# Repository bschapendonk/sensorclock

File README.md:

# sensorclock

I'm a software engineer by trade and I was looking for a nice project to use [Windows 10 IoT Core](https://dev.windows.com/en-us/iot) running on a Raspberry Pi 2 Model B.
So I decided on an clock inspired by Steve Gardner's [6 Digit LED Clock](http://sdgelectronics.co.uk/ledclock-projects/) project.
Initially I only planned on the clock, but I ended up addeding a bunch of sensors that might be used for some "IoT" in the feature.

Everything is controlled thru I2C, except the RGB leds which use SPI, some GPIO's for the rotary encoder, interrupts from the sensors and control lines to turn off the +3V3 (to reset all I2C devices). Basically any MCU that has I2C, SPI and some GPIO's can be used.

*The new Raspberry Pi 3 is pin compatible and runs even better*

* [Schematic](/hardware/pdf/sensorclock.pdf)
* [Board Top](/hardware/pdf/sensorclock_top.pdf)
* [Board Bottom](/hardware/pdf/sensorclock_bottom.pdf)
* [Gerbers](/hardware/gerber)

## things learned / improvements / mistakes
* U2 has an invalid I2C address
 * [Workaround] Use ALLCALL to enable SUBADDR1 on all PCA9622's, then disable SUBADDR1 on the good addressed PCA9622's and use SUBADDR1 to address the wrong addressed U2
* The MCP3425 and DS3231 have the same I2C address #fail
 * [Workaround] For now I cut the SDA/SCL traces to the DS3231
* The interconnect between te sensorclock and the Raspberrry Pi 2
 * This is a custom cable which saved time in design process of the board (less complex routing), but in hindsight this was a mistake since the assembly of the cable is quite difficult and error prone.
 
## features
* Windows 10 IoT Core controlled
* Six 7-segment 70mm (2.3") high displays
* Eight APA102C serial controlled RGB led's for ambient lighting or mood indication
* Temperature, humidity, barometric pressure, ambient light and air quality sensors
* Mechanical rotary encoder with switch for user input

## components
* Raspberry Pi 2 Model B
* ~~DS3231 [http://datasheets.maximintegrated.com/en/ds/DS3231.pdf]~~ (address conflict)
* PEC16 [http://www.bourns.com/data/global/pdfs/pec16.pdf]
* APA102C [http://www.adafruit.com/datasheets/APA102.pdf]

### clock
* PCA9622 [http://www.nxp.com/documents/data_sheet/PCA9622.pdf]
* SA23-11SRWA [http://www.kingbrightusa.com/images/catalog/spec/SA23-11SRWA.pdf]

### sensors
* SparkFun Atmospheric Sensor Breakout - BME280 [https://www.sparkfun.com/products/13676]
* SparkFun Luminosity Sensor Breakout - TSL2561 [https://www.sparkfun.com/products/12055]
* MQ-135 air quality sensor, ADC and loadswitch
 * MCP3425 [http://ww1.microchip.com/downloads/en/DeviceDoc/22072b.pdf]
 * AP2280 [http://www.diodes.com/_files/datasheets/AP2280.pdf]

**!!This is a work in progress, use at your own risk!!**

## renders

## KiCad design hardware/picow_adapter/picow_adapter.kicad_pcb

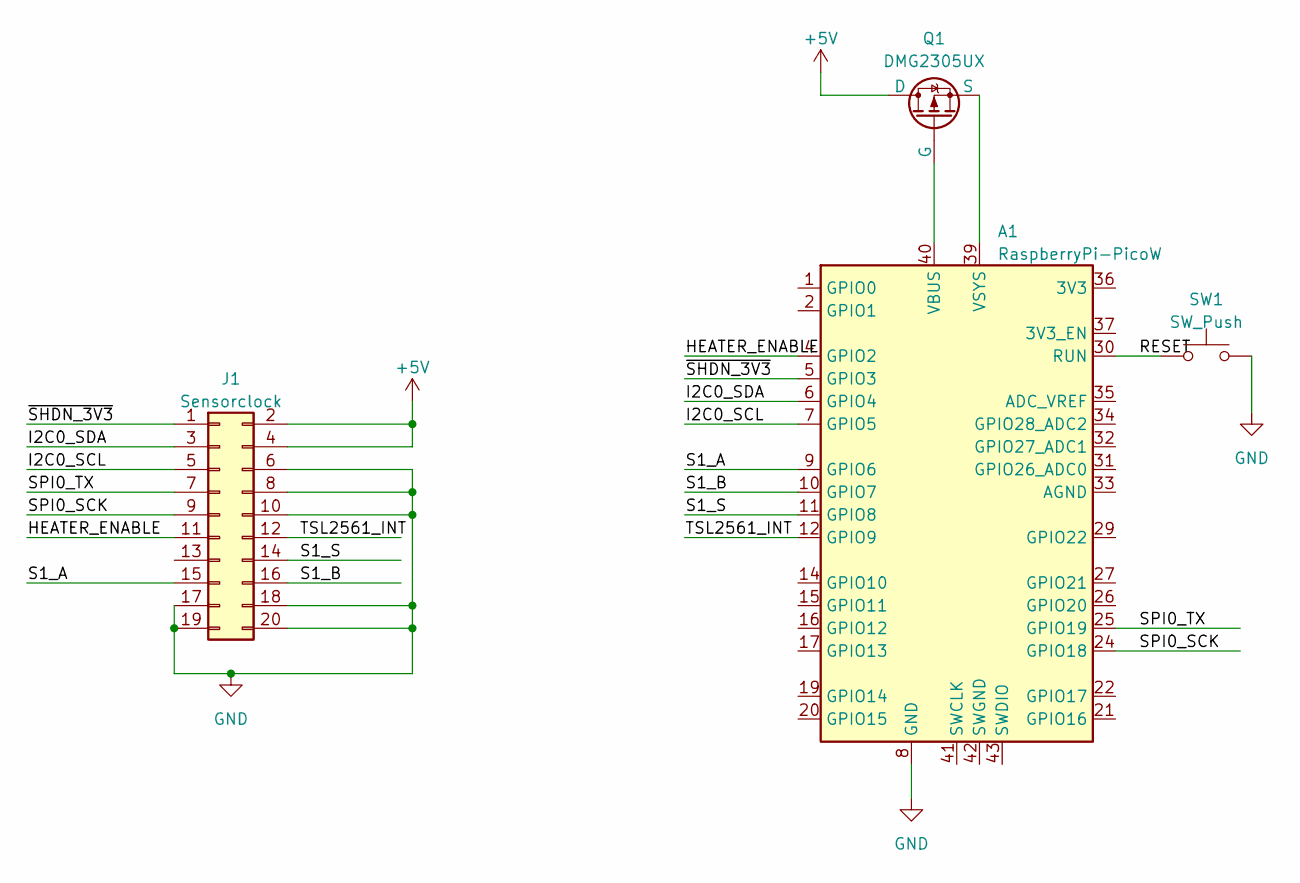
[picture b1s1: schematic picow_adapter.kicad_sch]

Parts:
A1: RaspberryPi-PicoW; Raspberry_Pi_Pico_SMT_THT
J1: Sensorclock; PinSocket_2x10_P2.54mm_Vertical
Q1: DMG2305UX; SOT-23
SW1: SW_Push; SW_SPST_B3U-1000P

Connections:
+5V: J1.2, J1.4, Q1.3 (D)
/HEATER_ENABLE: A1.4 (GPIO2), J1.11
/I2C0_SCL: A1.7 (GPIO5), J1.5
/I2C0_SDA: A1.6 (GPIO4), J1.3
/RESET: A1.30 (RUN), SW1.1
/S1_A: A1.9 (GPIO6), J1.15
/S1_B: A1.10 (GPIO7), J1.16
/S1_S: A1.11 (GPIO8), J1.14
/SPI0_SCK: A1.24 (GPIO18), J1.9
/SPI0_TX: A1.25 (GPIO19), J1.7
/TSL2561_INT: A1.12 (GPIO9), J1.12
/~SHDN_3V3: A1.5 (GPIO3), J1.1
GND: A1.3 (GND), A1.8 (GND), A1.13 (GND), A1.18 (GND), A1.23 (GND), A1.28 (GND), A1.38 (GND), J1.6, J1.8, J1.10, J1.17, J1.18, J1.19, J1.20, SW1.2
unnamed: A1.40 (VBUS), Q1.1 (G)
unnamed: A1.39 (VSYS), Q1.2 (S)

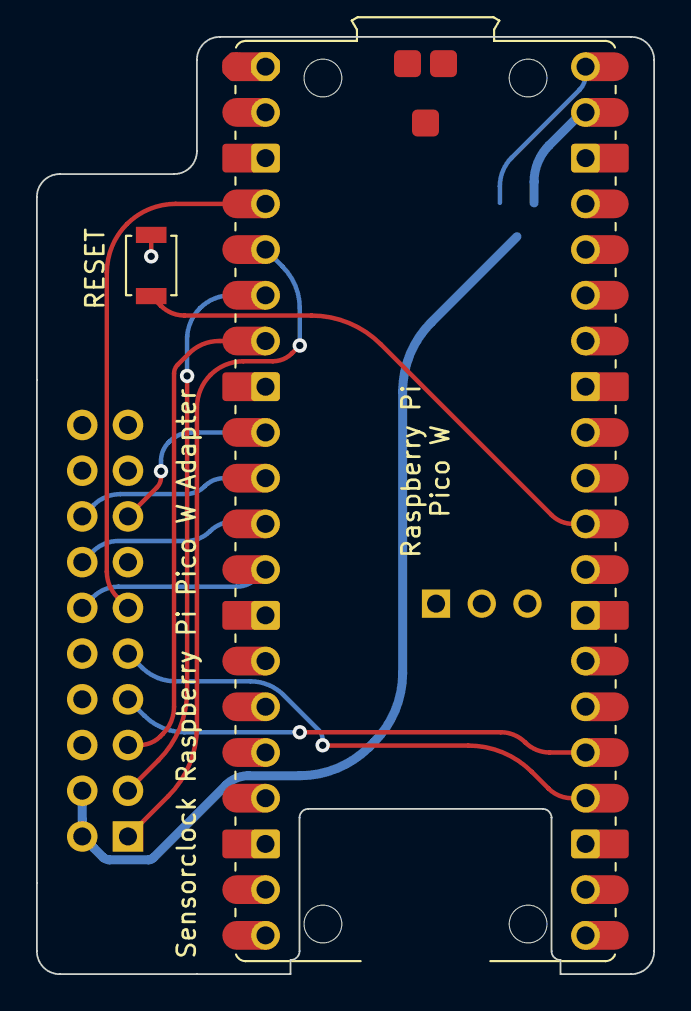
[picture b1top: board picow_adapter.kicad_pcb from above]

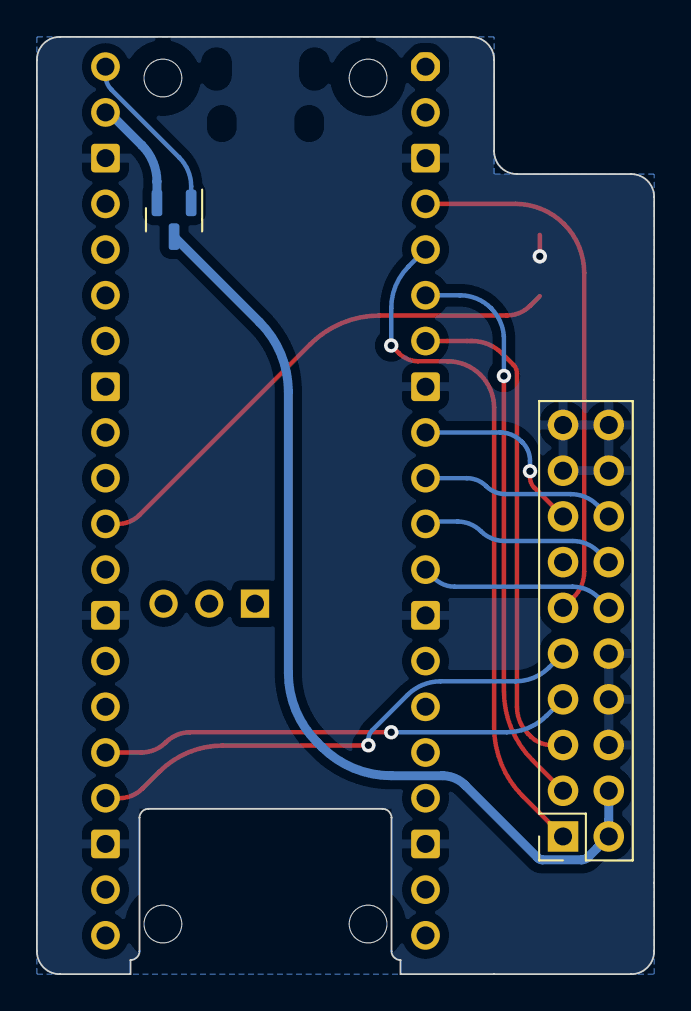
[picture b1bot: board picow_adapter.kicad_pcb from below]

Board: 2 copper layers, 34.3 x 52.1 mm, 4 parts (2 on the bottom side), 15 nets.

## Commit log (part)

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2015-11-09 import
2015-11-15 Fixed an addressing issue with the PCA9622
2015-11-22 inital import
2015-11-22 test programm
2016-02-26 inital
2016-04-12 Microsoft.NETCore.UniversalWindowsPlatform 5.1.0
2016-06-27 Microsoft.NETCore.UniversalWindowsPlatform 5.2.0
2016-07-19 Microsoft.NETCore.UniversalWindowsPlatform 5.2.2
2016-08-09 Target Windows 10 AU
2017-02-21 Microsoft.NETCore.UniversalWindowsPlatform 5.3.0
2017-03-14 Microsoft.NETCore.UniversalWindowsPlatform 5.3.1
2017-04-06 Target 10.0.15063.0
2017-04-11 Microsoft.NETCore.UniversalWindowsPlatform 5.3.2
2017-04-25 Microsoft.NETCore.UniversalWindowsPlatform 5.3.3
2017-04-25 conversion to PackageReference codemaid cleanupall
2017-08-08 Microsoft.NETCore.UniversalWindowsPlatform 5.3.4
2017-08-15 Microsoft.NETCore.UniversalWindowsPlatform 5.4.0
2017-09-01 small improvement
2017-09-01 crude rainbow effect
2017-09-01 timing
2017-10-15 Microsoft.NETCore.UniversalWindowsPlatform 6.0.1
2017-10-19 TargetPlatform 10.0.16299.0
2017-11-22 Microsoft.NETCore.UniversalWindowsPlatform 6.0.2
2017-12-05 Microsoft.NETCore.UniversalWindowsPlatform 6.0.4
2017-12-13 Microsoft.NETCore.UniversalWindowsPlatform 6.0.5
2018-01-10 Microsoft.NETCore.UniversalWindowsPlatform 6.0.6
2018-02-13 Microsoft.NETCore.UniversalWindowsPlatform 6.0.7
2018-05-08 target 10.0.17134.0
2018-05-17 Microsoft.NETCore.UniversalWindowsPlatform 6.1.4
2018-07-03 Microsoft.NETCore.UniversalWindowsPlatform 6.1.5
2018-08-03 Microsoft.NETCore.UniversalWindowsPlatform 6.1.7
2018-10-10 TargetPlatformVersion 10.0.17763.0 Microsoft.NETCore.UniversalWindowsPlatform 6.1.9
2018-12-11 Microsoft.NETCore.UniversalWindowsPlatform 6.2.2
2019-06-12 Microsoft.NETCore.UniversalWindowsPlatform 6.2.8
2021-10-12 .net 6.0 rc2
2021-11-08 .net 6.0 :)
2022-09-22 .NET 7 rc1
2022-09-22 update pipeline
2022-11-16 Raspberry Pi 4B get! Hello World ARM64!
2023-03-23 net8.0 let's GO
2023-03-23 test
2023-03-23 revert
2025-03-19 Update Microsoft.Extensions.Hosting.Systemd package version
    Updated the version of the `Microsoft.Extensions.Hosting.Systemd` package in the `Directory.Packages.props` file from `10.0.0-preview.1.25080.5` to `10.0.0-preview.2.25163.2`.
2025-04-13 Update Microsoft.Extensions.Hosting.Systemd package version
    Updated the version of the `Microsoft.Extensions.Hosting.Systemd` package from `10.0.0-preview.2.25163.2` to `10.0.0-preview.3.25171.5` in the `Directory.Packages.props` file.
2025-05-13 Update Microsoft.Extensions.Hosting.Systemd package version
    Updated the version of the `Microsoft.Extensions.Hosting.Systemd` package in the `Directory.Packages.props` file from `10.0.0-preview.3.25171.5` to `10.0.0-preview.4.25258.110`.
2025-05-14 Revert Microsoft.Extensions.Hosting.Systemd package version to 9.0.5 and update target framework to net9.0
2025-05-14 Restore .NET version to 9 in GitHub Actions workflow
2025-05-15 Fix artifact path to target .NET 9.0 in GitHub Actions workflow
2025-06-13 Update package versions in Directory.Packages.props
    Updated `Iot.Device.Bindings` to version `4.0.1` and
    `Microsoft.Extensions.Hosting.Systemd` to version `9.0.6`.
2025-07-31 Update Microsoft.Extensions.Hosting.Systemd to 9.0.7
    Updated the version of the package `Microsoft.Extensions.Hosting.Systemd` from `9.0.6` to `9.0.7` in the `Directory.Packages.props` file.
2025-08-28 Update actions/checkout to version 5 in GitHub Actions workflow
2025-09-02 Update Microsoft.Extensions.Hosting.Systemd to 9.0.8
    Updated the version of the package `Microsoft.Extensions.Hosting.Systemd` from `9.0.7` to `9.0.8` in the `Directory.Packages.props` file.
2025-09-12 Update Microsoft.Extensions.Hosting.Systemd to 9.0.9
    Updated the version of the package `Microsoft.Extensions.Hosting.Systemd` from `9.0.8` to `9.0.9` in the `Directory.Packages.props` file.
2025-10-20 Update Microsoft.Extensions.Hosting.Systemd to 9.0.10
    Updated the `Directory.Packages.props` file to increment the
    version of the `Microsoft.Extensions.Hosting.Systemd` package
    from `9.0.9` to `9.0.10`. This ensures the project benefits
    from any bug fixes, performance improvements, or new features
    introduced in the updated version. No other package versions
    were modified.
2025-10-20 Update actions/setup-dotnet to version 5 and change dotnet version to 10
2025-11-12 Remove commented dotnet-quality option in workflow configuration
2025-12-09 Update Microsoft.Extensions.Hosting.Systemd to 10.0.1
    Updated the `Microsoft.Extensions.Hosting.Systemd` package version in the `Directory.Packages.props` file from `10.0.0` to `10.0.1`. This minor version update likely includes bug fixes or small impro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
2025-12-22 Upgrade GitHub Actions to latest versions
2026-03-18 #
    Update NuGet package versions for Iot and Systemd
    Upgraded Iot.Device.Bindings from 4.0.1 to 4.1.0 and Microsoft.Extensions.Hosting.Systemd from 10.0.1 to 10.0.5 to include the latest features and fixes.
2026-04-01 Update Iot.Device.Bindings to version 4.2.0
    Upgraded the Iot.Device.Bindings NuGet package from version 4.1.0 to 4.2.0 in Directory.Packages.props to incorporate the latest features and fixes. No other dependencies were changed.
2026-04-15 Update Systemd package to version 10.0.6
    Upgraded Microsoft.Extensions.Hosting.Systemd from 10.0.5 to 10.0.6 in Directory.Packages.props to ensure the latest fixes and improvements are included. No other dependencies were changed.
2026-05-26 Update Systemd package to version 10.0.8
    Upgraded Microsoft.Extensions.Hosting.Systemd NuGet package from version 10.0.6 to 10.0.8 in Directory.Packages.props to ensure compatibility and receive the latest fixes and improvements.
2026-06-26 Update CI actions and Systemd package version
    Upgraded actions/checkout and actions/upload-artifact to v7 in main.yml. Bumped Microsoft.Extensions.Hosting.Systemd to 10.0.9 in Directory.Packages.props.
